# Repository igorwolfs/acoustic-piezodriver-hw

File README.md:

# Acoustic Piezodriver HW

This board generates the signal used to excite the piezo-module. Excitation frequencies are between 100 kHz and 10 MHz. All above 5 MHz will probably be hard to reach, given the component specs had to be balanced with price.

## 40V BOOST
Supplies the single-phase inverter with a 40 V voltage, given a 20 V input voltage.

## 6V SEPIC
Supplies around 6 V to the PCONN 5V connector. Meant to supply power to the acoustic-processing-hw board.

## 10 V SEPIC
Supplies the FET-drivers with a steady 10V.

## SIGCONN
Drives the PWM signals, enables the 40V BOOST and the 10V SEPIC, contains an SPI bus meant to control the on-board ADC and temperature sensors. Meant to be connected to the acoustic-processing-hw board.

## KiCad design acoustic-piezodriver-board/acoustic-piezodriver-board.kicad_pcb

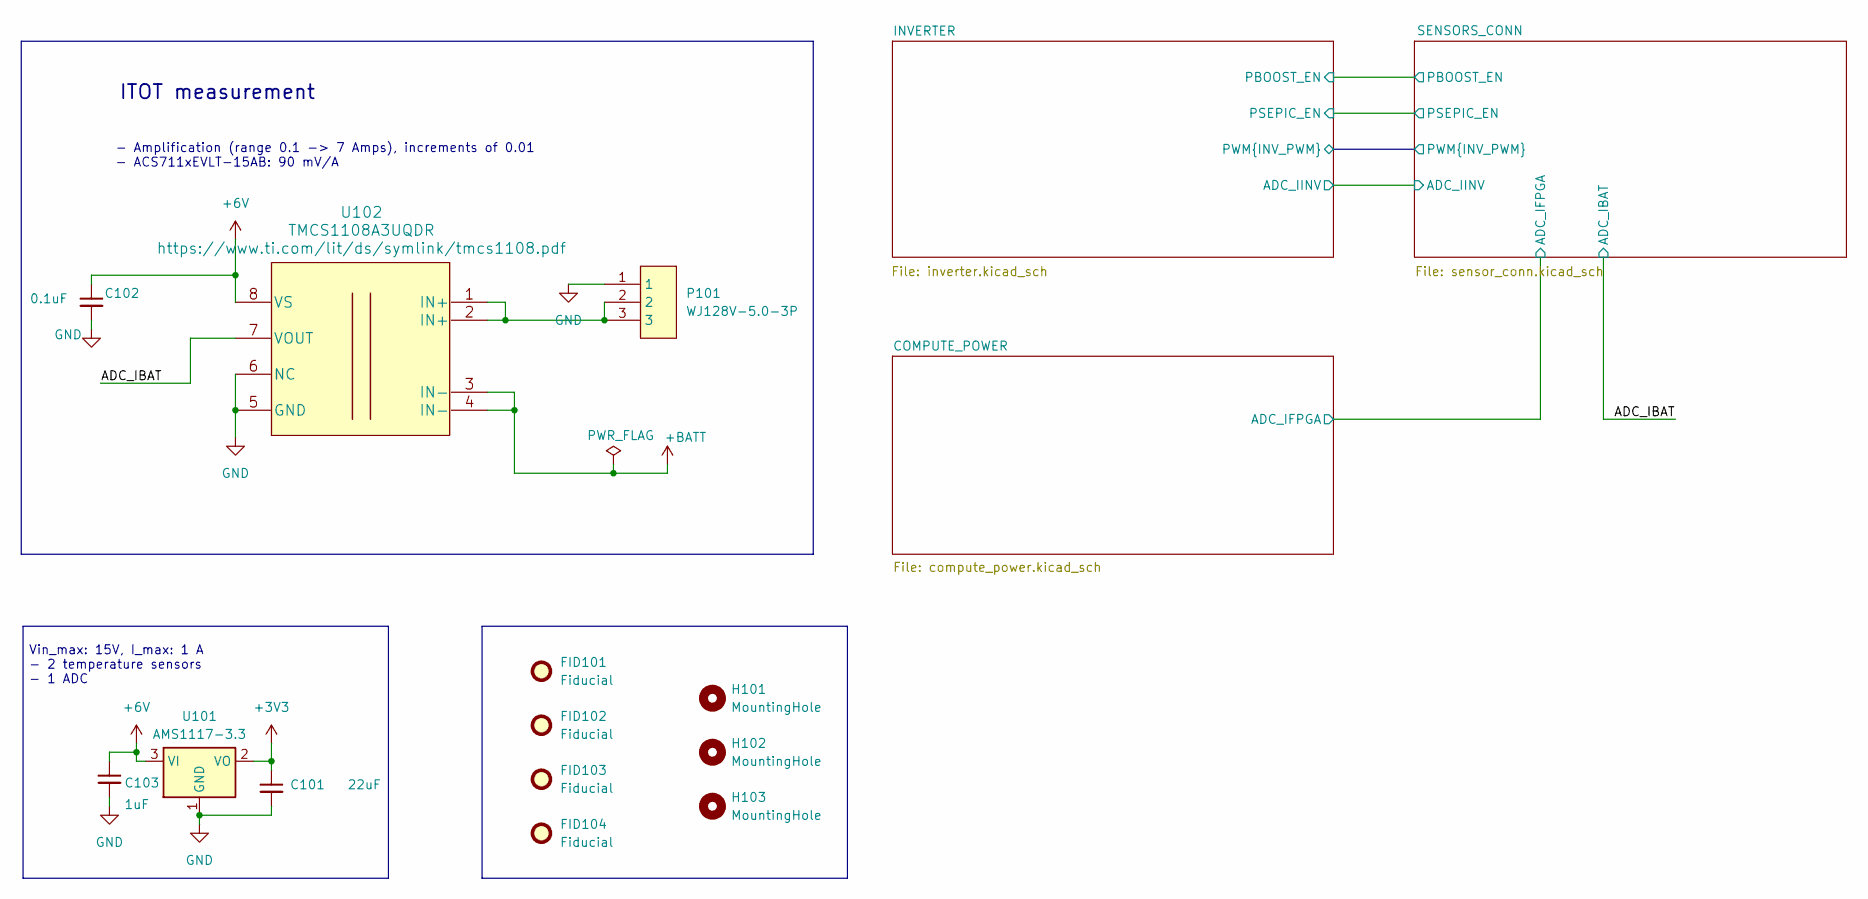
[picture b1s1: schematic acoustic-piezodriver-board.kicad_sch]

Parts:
C101: 22uF; C_0805_2012Metric; Manufacturing Part Numb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 CL21A226MAQNNNE; LCSC Part Number C45783
C102: 0.1uF; C_0402_1005Metric; Manufacturing Part Numb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 CL05B104KB54PNC; LCSC Part Number C307331
C103: 1uF; C_0805_2012Metric; Manufacturing Part Numb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 CL21B105KBFNNNE; LCSC Part Number C28323
FID101, FID102, FID103, FID104: Fiducial; Fiducial_1mm_Mask2mm
H101, H102, H103: MountingHole; ToolingHole_1.152mm
P101: WJ128V-5.0-3P; Manufacturing Part Numb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 WJ128V-5.0-3P; LCSC Part Number C8270
U101: AMS1117-3.3; SOT-223-3_TabPin2; Manufacturing Part Numb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 AMS1117-3.3; LCSC Part Number C6186
U102: TMCS1108A3UQDR; Manufacturing Part Numb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 TMCS1108A3UQDR; LCSC Part Number C3684263

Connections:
+3V3: C101.1, U101.2 (VO); also elsewhere on the board
+6V: C102.1, C103.1, U101.3 (VI), U102.8 (VS); also elsewhere on the board
+BATT: U102.3 (IN-), U102.4 (IN-); also elsewhere on the board
/ADC_IBAT: U102.7 (VOUT); also elsewhere on the board
GND: C101.2, C102.2, C103.2, P101.1, U101.1 (GND), U102.5 (GND), U102.6 (NC); also elsewhere on the board
unnamed: P101.2, P101.3, U102.1 (IN+), U102.2 (IN+)

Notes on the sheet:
ITOT measurement
- Amplification (range 0.1 -> 7 Amps), increments of 0.01 - ACS711xEVLT-15AB: 90 mV/A
Vin_max: 15V, I_max: 1 A - 2 temperature sensors - 1 ADC

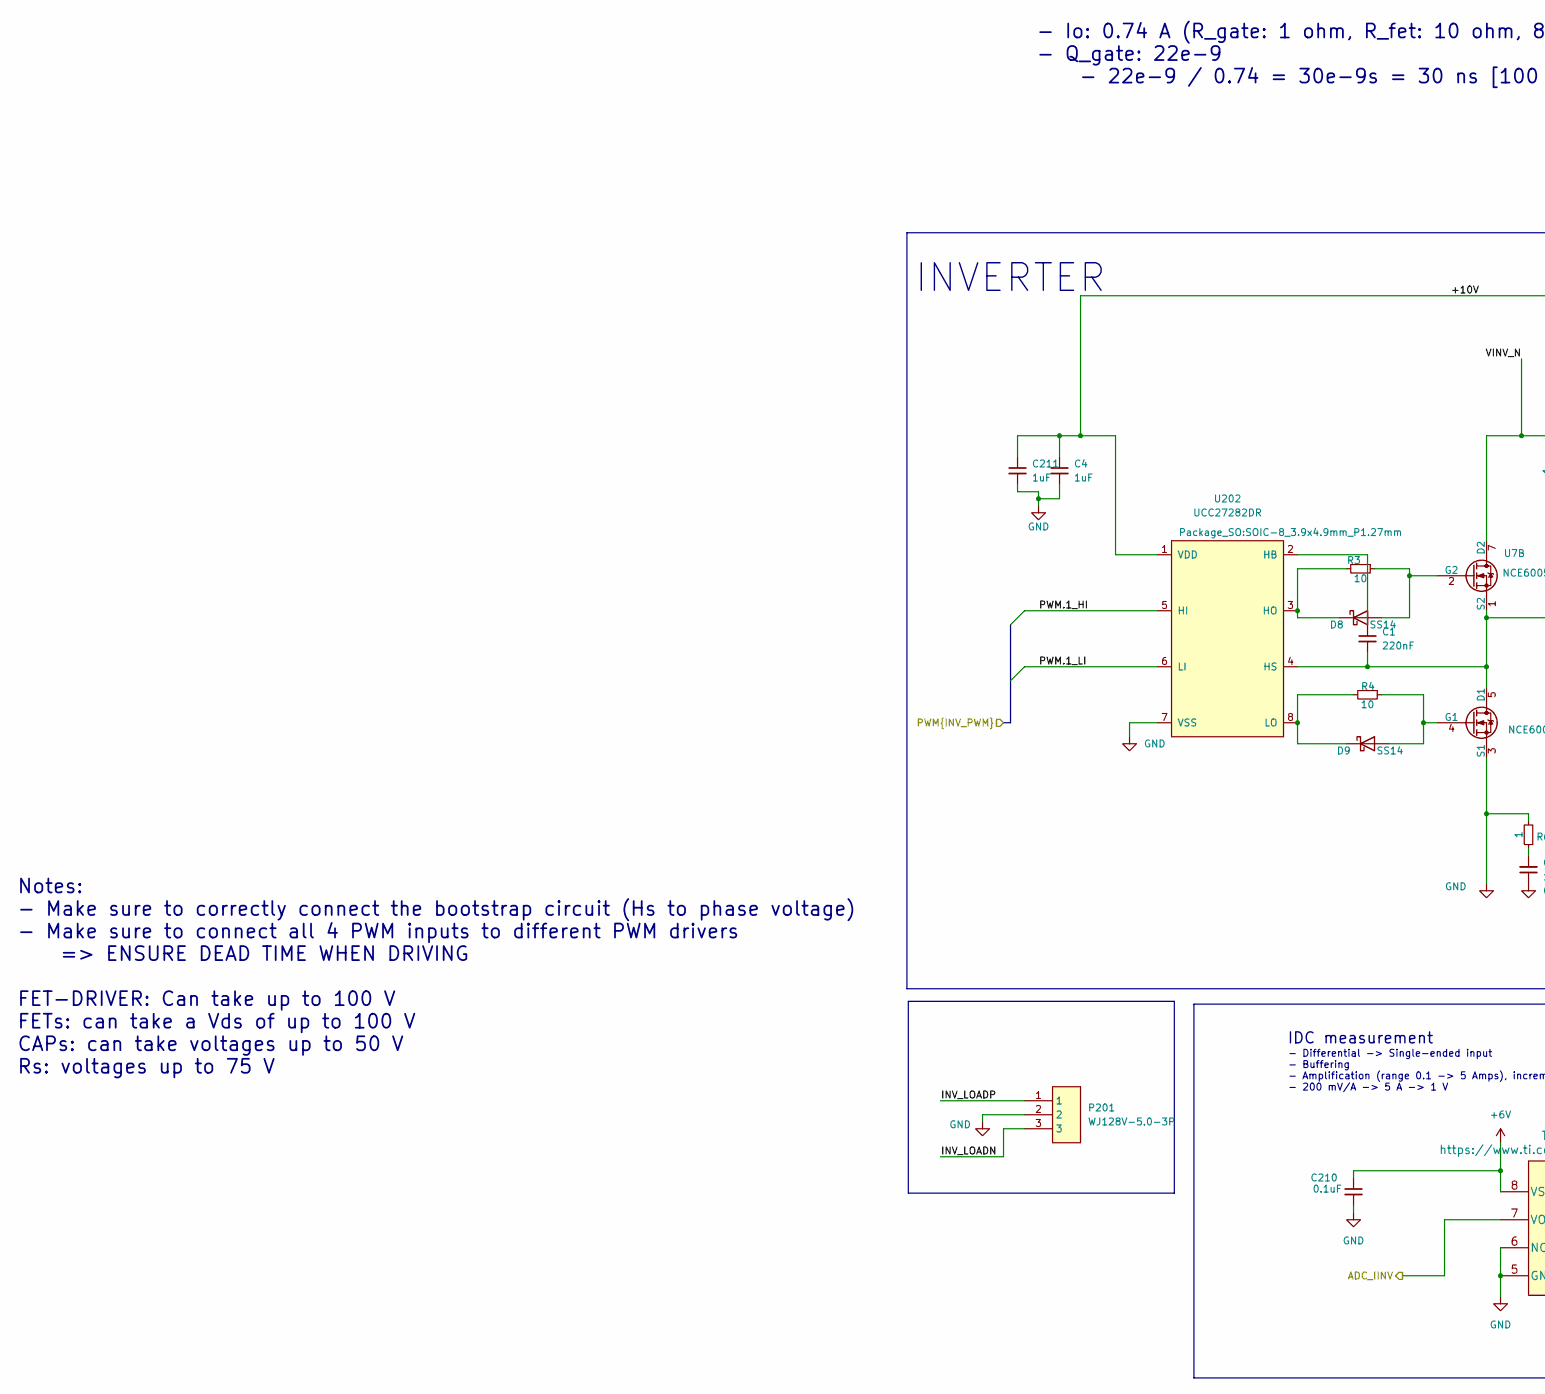
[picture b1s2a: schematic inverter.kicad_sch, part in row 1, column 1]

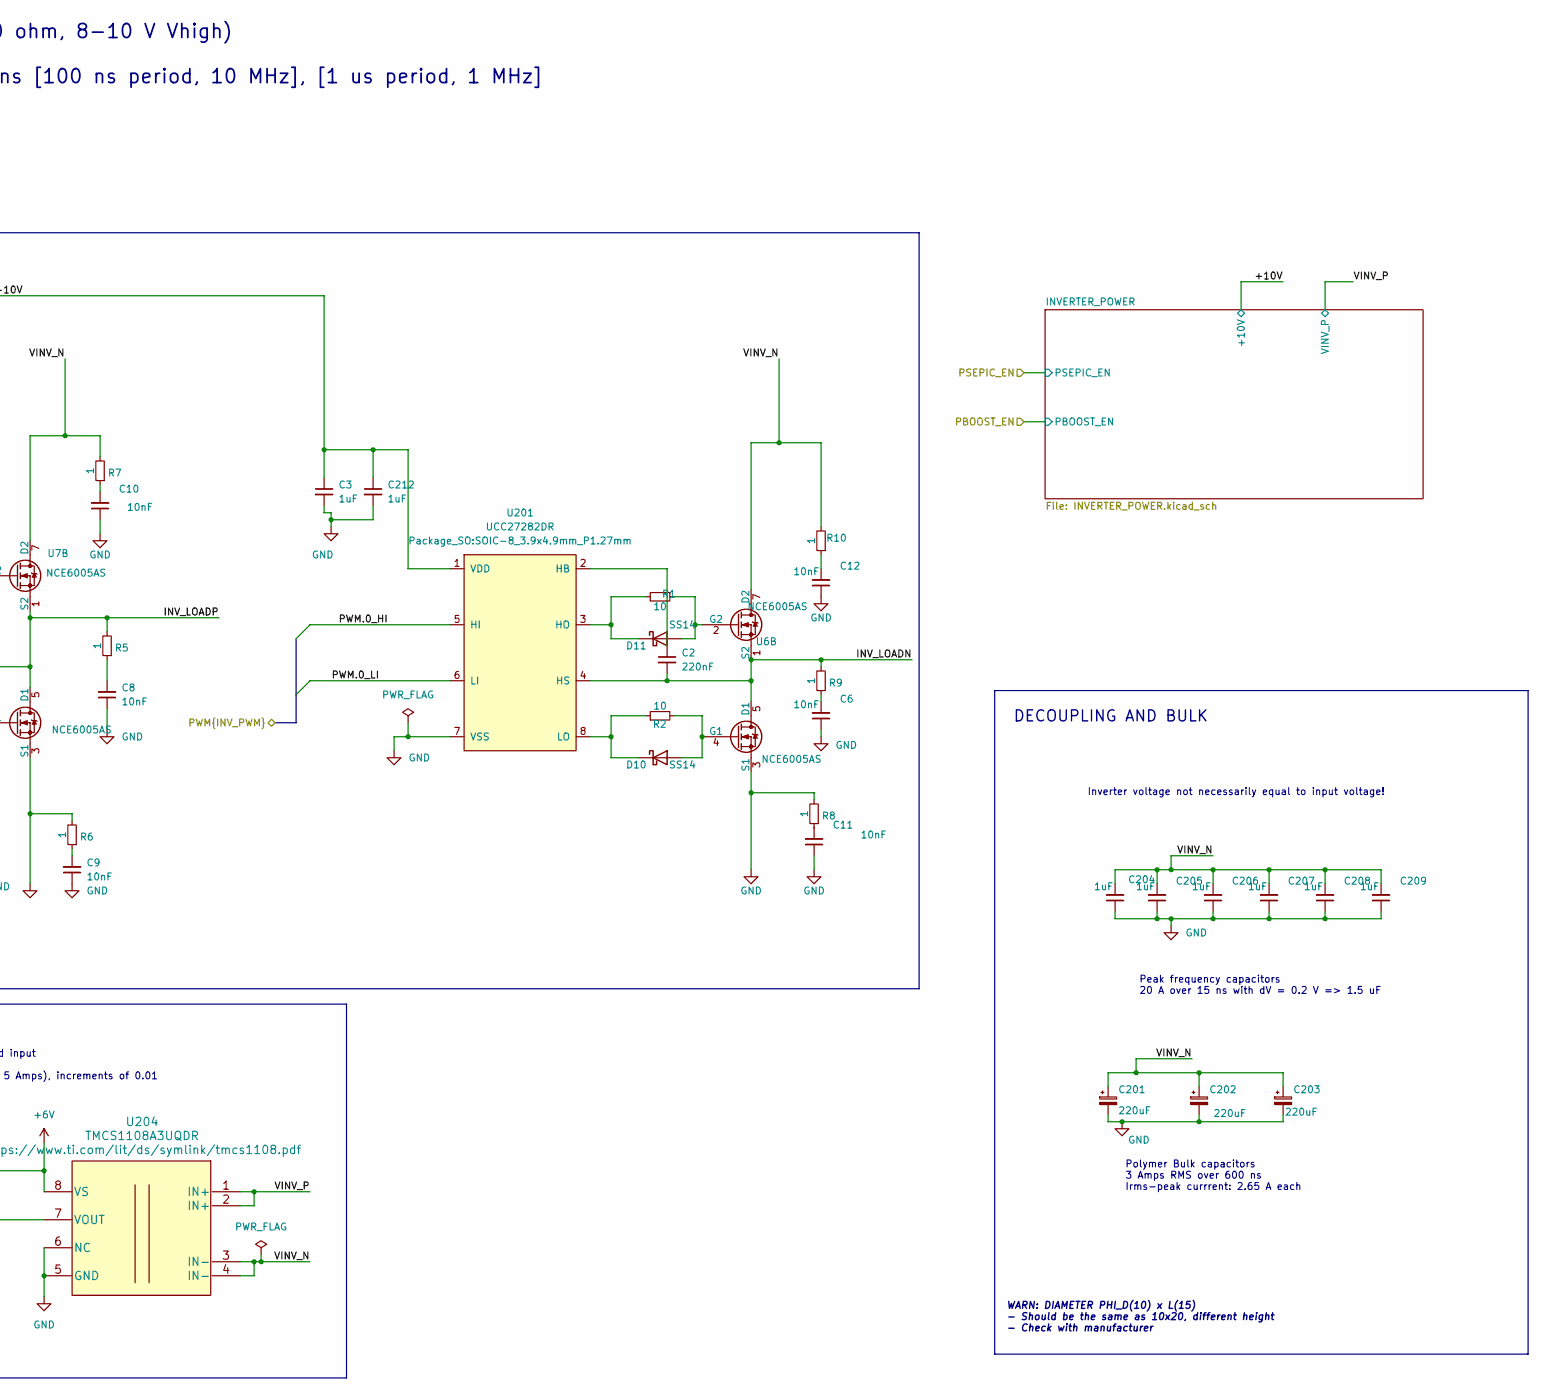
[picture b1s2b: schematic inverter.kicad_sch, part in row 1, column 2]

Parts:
C1, C2: 220nF; C_0805_2012Metric; Manufacturing Part Numb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 CL21B224KBFNNNE; LCSC Part Number C5378
C3, C4, C204, C205, C206, C207, C208, C209, C211, C212: 1uF; C_0805_2012Metric; Manufacturing Part Numb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 CL21B105KBFNNNE; LCSC Part Number C28323
C6, C8, C9, C10, C11, C12: 10nF; C_0402_1005Metric; Manufacturing Part Numb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 CL05B103KB5NNNC; LCSC Part Number C15195
C201, C202, C203: 220uF; C_Radial_D10.0mm_H16.0mm_P5.00mm; Manufacturing Part Numb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 SPZ1JM221G15O00RAXXX; LCSC Part Number C2983797
C210: 0.1uF; C_0402_1005Metric; Manufacturing Part Numb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 CL05B104KB54PNC; LCSC Part Number C307331
D8, D9, D10, D11: SS14; D_SMA; Manufacturing Part Numb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 SS14; LCSC Part Number C2480
P201: WJ128V-5.0-3P; Manufacturing Part Numb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 WJ128V-5.0-3P; LCSC Part Number C8270
R1, R2, R3, R4: 10; R_1206_3216Metric; Manufacturing Part Numb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 1206W4F100JT5E; LCSC Part Number C17903
R5, R6, R7, R8, R9, R10: 1; R_0603_1608Metric; Manufacturing Part Numb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 0603WAF100KT5E; LCSC Part Number C22936
U6, U7: NCE6005AS; SOIC-8_3.9x4.9mm_P1.27mm; Manufacturing Part Numb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 NCE6005AS; LCSC Part Number C126151
U201, U202: UCC27282DR; SOIC-8_3.9x4.9mm_P1.27mm; Manufacturing Part Numb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 UCC27282DR; LCSC Part Number C2867844
U204: TMCS1108A3UQDR; Manufacturing Part Numb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 TMCS1108A3UQDR; LCSC Part Number C3684263

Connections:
+6V: C210.1, U204.8 (VS); also elsewhere on the board
/INVERTER/+10V: C3.1, C4.1, C211.1, C212.1, U201.1 (VDD), U202.1 (VDD); also elsewhere on the board
/INVERTER/ADC_IINV: U204.7 (VOUT); also elsewhere on the board
/INVERTER/INV_LOADN: C2.2, P201.3, R9.2, U6.1 (S2), U6.5 (D1), U6.6 (D1), U201.4 (HS)
/INVERTER/INV_LOADP: C1.2, P201.1, R5.2, U7.1 (S2), U7.5 (D1), U7.6 (D1), U202.4 (HS)
/INVERTER/PWM.0_HI: U201.5 (HI); also elsewhere on the board
/INVERTER/PWM.0_LI: U201.6 (LI); also elsewhere on the board
/INVERTER/PWM.1_HI: U202.5 (HI); also elsewhere on the board
/INVERTER/PWM.1_LI: U202.6 (LI); also elsewhere on the board
/INVERTER/VINV_N: C201.1, C202.1, C203.1, C204.2, C205.2, C206.2, C207.2, C208.2, C209.2, R7.2, R10.2, U6.7 (D2), U6.8 (D2), U7.7 (D2), U7.8 (D2), U204.3 (IN-), U204.4 (IN-)
/INVERTER/VINV_P: U204.1 (IN+), U204.2 (IN+); also elsewhere on the board
GND: C3.2, C4.2, C6.1, C8.1, C9.1, C10.1, C11.1, C12.1, C201.2, C202.2, C203.2, C204.1, C205.1, C206.1, C207.1, C208.1, C209.1, C210.2, C211.2, C212.2, P201.2, R6.2, R8.2, U6.3 (S1), U7.3 (S1), U201.7 (VSS), U202.7 (VSS), U204.5 (GND), U204.6 (NC); also elsewhere on the board
unnamed: C6.2, R9.1
unnamed: C8.2, R5.1
unnamed: C9.2, R6.1
unnamed: C10.2, R7.1
unnamed: C11.2, R8.1
unnamed: C12.2, R10.1
unnamed: D8.2 (A), R3.1, U7.2 (G2)
unnamed: D8.1 (K), R3.2, U202.3 (HO)
unnamed: D9.2 (A), R4.1, U7.4 (G1)
unnamed: D9.1 (K), R4.2, U202.8 (LO)
unnamed: D10.2 (A), R2.2, U6.4 (G1)
unnamed: D10.1 (K), R2.1, U201.8 (LO)
unnamed: D11.2 (A), R1.1, U6.2 (G2)
unnamed: D11.1 (K), R1.2, U201.3 (HO)
unnamed: C2.1, U201.2 (HB)
unnamed: C1.1, U202.2 (HB)

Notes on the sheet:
- Io: 0.74 A (R_gate: 1 ohm, R_fet: 10 ohm, 8-10 V Vhigh) - Q_gate: 22e-9 - 22e-9 / 0.74 = 30e-9s = 30 ns [100 ns period, 10 MHz], [1 us period, 1 MHz]
DECOUPLING AND BULK
INVERTER
Peak frequency capacitors 20 A over 15 ns with dV = 0.2 V => 1.5 uF
- Differential -> Single-ended input - Buffering - Amplification (range 0.1 -> 5 Amps), increments of 0.01 - 200 mV/A -> 5 A -> 1 V
Notes: - Make sure to correctly connect the bootstrap circuit (Hs to phase voltage) - Make sure to connect all 4 PWM inputs to different PWM drivers => ENSURE DEAD TIME WHEN DRIVING FET-DRIVER: Can take up to 100 V FETs: can take a Vds of up to 100 V CAPs: can take voltages up to 50 V Rs: voltages 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
Polymer Bulk capacitors 3 Amps RMS over 600 ns Irms-peak currrent: 2.65 A each
Inverter voltage not necessarily equal to input voltage!
WARN: DIAMETER PHI_D(10) x L(15) - Should be the same as 10x20, different height - Check with manufacturer
IDC measurement

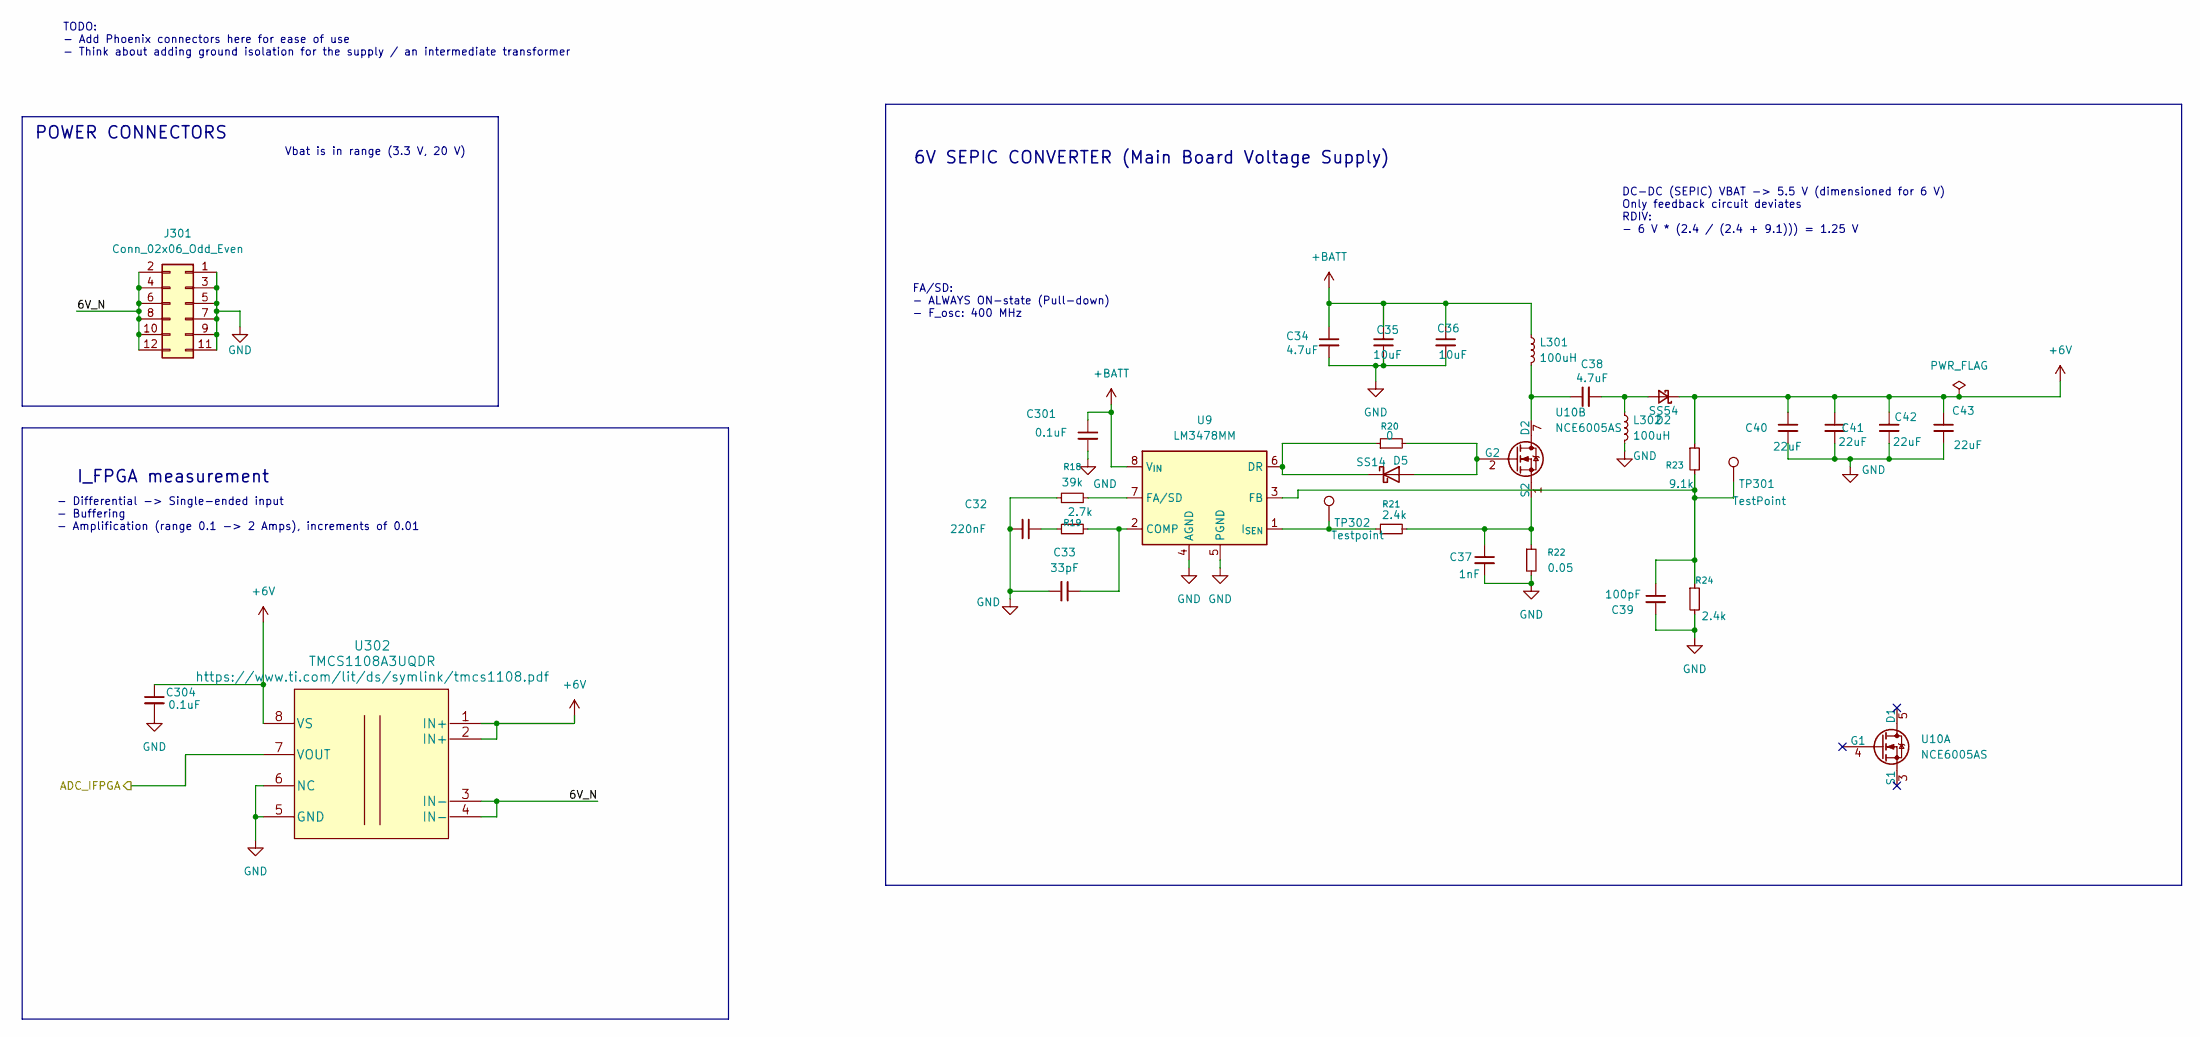
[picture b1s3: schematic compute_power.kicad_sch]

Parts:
C32: 220nF; C_0805_2012Metric; Manufacturing Part Numb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 CL21B224KBFNNNE; LCSC Part Number C5378
C33: 33pF; C_0603_1608Metric; Manufacturing Part Numb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 CL10C330JB8NNNC; LCSC Part Number C1663
C34, C38: 4.7uF; C_1206_3216Metric; Manufacturing Part Numb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 1206B475K500NT; LCSC Part Number C29823
C35, C36: 10uF; C_0805_2012Metric; Manufacturing Part Numb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 GRM21BR61H106KE43L; LCSC Part Number C440198
C37: 1nF; C_0402_1005Metric; Manufacturing Part Numb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 0402B102K500NT; LCSC Part Number C1523
C39: 100pF; C_0402_1005Metric; Manufacturing Part Numb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 0402CG101J500NT; LCSC Part Number C1546
C40, C41, C42, C43: 22uF; C_0805_2012Metric; Manufacturing Part Numb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 CL21A226MAQNNNE; LCSC Part Number C45783
C301, C304: 0.1uF; C_0402_1005Metric; Manufacturing Part Numb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 CL05B104KB54PNC; LCSC Part Number C307331
D2: SS54; D_SMA; Manufacturing Part Numb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 SS54; LCSC Part Number C22452
D5: SS14; D_SMA; Manufacturing Part Numb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 SS14; LCSC Part Number C2480
J301: Conn_02x06_Odd_Even; PinHeader_2x06_P2.54mm_Vertical; Manufacturing Part Numb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 B-2100S12P-B110; LCSC Part Number C124388
L301, L302: 100uH; PSPMAA1050H-101M-ANP; Manufacturing Part Numb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 PSPMAA1050H-101M-ANP; LCSC Part Number C5273830
R18: 39k; R_0603_1608Metric; Manufacturing Part Numb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 0603WAF3902T5E; LCSC Part Number C23153
R19: 2.7k; R_0603_1608Metric; Manufacturing Part Numb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 0603WAF2701T5E; LCSC Part Number C13167
R20: 0; R_0603_1608Metric_Pad0.98x0.95mm_HandSolder; Manufacturing Part Numb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 0603WAJ0000T5E; LCSC Part Number C15402
R21: 2.4k; R_0805_2012Metric_Pad1.20x1.40mm_HandSolder; Manufacturing Part Numb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 0805W8F2401T5E; LCSC Part Number C17526
R22: 0.05; R_1206_3216Metric_Pad1.30x1.75mm_HandSolder; Manufacturing Part Numb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 1206W3F500MT5E; LCSC Part Number C127691
R23: 9.1k; R_0603_1608Metric; Manufacturing Part Numb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 0603WAF9101T5E; LCSC Part Number C23260
R24: 2.4k; R_0603_1608Metric; Manufacturing Part Numb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 0603WAF2401T5E; LCSC Part Number C22940
TP301: TestPoint; TestPoint_Pad_D1.0mm
TP302: Testpoint; TestPoint_Pad_D1.0mm
U9: LM3478MM; VSSOP-8_3x3mm_P0.65mm; Manufacturing Part Numb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 LM3478MMX/NOPB; LCSC Part Number C404045
U10: NCE6005AS; SOIC-8_3.9x4.9mm_P1.27mm; Manufacturing Part Numb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 NCE6005AS; LCSC Part Number C126151
U302: TMCS1108A3UQDR; Manufacturing Part Numb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 TMCS1108A3UQDR; LCSC Part Number C3684263

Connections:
+6V: C40.1, C41.1, C42.1, C43.1, C304.1, D2.1 (K), R23.1, U302.1 (IN+), U302.2 (IN+), U302.8 (VS); also elsewhere on the board
+BATT: C34.1, C35.1, C36.1, C301.1, L301.1, U9.8 (V_{IN}); also elsewhere on the board
/COMPUTE_POWER/6V_N: J301.2, J301.4, J301.6, J301.8, J301.10, J301.12, U302.3 (IN-), U302.4 (IN-)
/COMPUTE_POWER/ADC_IFPGA: U302.7 (VOUT); also elsewhere on the board
GND: C32.2, C33.2, C34.2, C35.2, C36.2, C37.2, C39.2, C40.2, C41.2, C42.2, C43.2, C301.2, C304.2, J301.1, J301.3, J301.5, J301.7, J301.9, J301.11, L302.2, R18.1, R22.2, R24.2, U9.4 (AGND), U9.5 (PGND), U302.5 (GND), U302.6 (NC); also elsewhere on the board
unnamed: C32.1, R19.1
unnamed: C38.1, L301.2, U10.7 (D2), U10.8 (D2)
unnamed: C38.2, D2.2 (A), L302.1
unnamed: D5.2 (A), R20.2, U10.2 (G2)
unnamed: D5.1 (K), R20.1, U9.6 (DR)
unnamed: C33.1, R19.2, U9.2 (COMP)
unnamed: R18.2, U9.7 (FA/SD)
unnamed: C39.1, R23.2, R24.1, TP301.1, U9.3 (FB)
unnamed: R21.1, TP302.1, U9.1 (I_{SEN})
unnamed: C37.1, R21.2, R22.1, U10.1 (S2)

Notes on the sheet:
POWER CONNECTORS
I_FPGA measurement
DC-DC (SEPIC) VBAT -> 5.5 V (dimensioned for 6 V) Only feedback circuit deviates RDIV: - 6 V * (2.4 / (2.4 + 9.1))) = 1.25 V
Vbat is in range (3.3 V, 20 V)
- Differential -> Single-ended input - Buffering - Amplification (range 0.1 -> 2 Amps), increments of 0.01
6V SEPIC CONVERTER (Main Board Voltage Supply)
TODO: - Add Phoenix connectors here for ease of use - Think about adding ground isolation for the supply / an intermediate transformer
FA/SD: - ALWAYS ON-state (Pull-down) - F_osc: 400 MHz

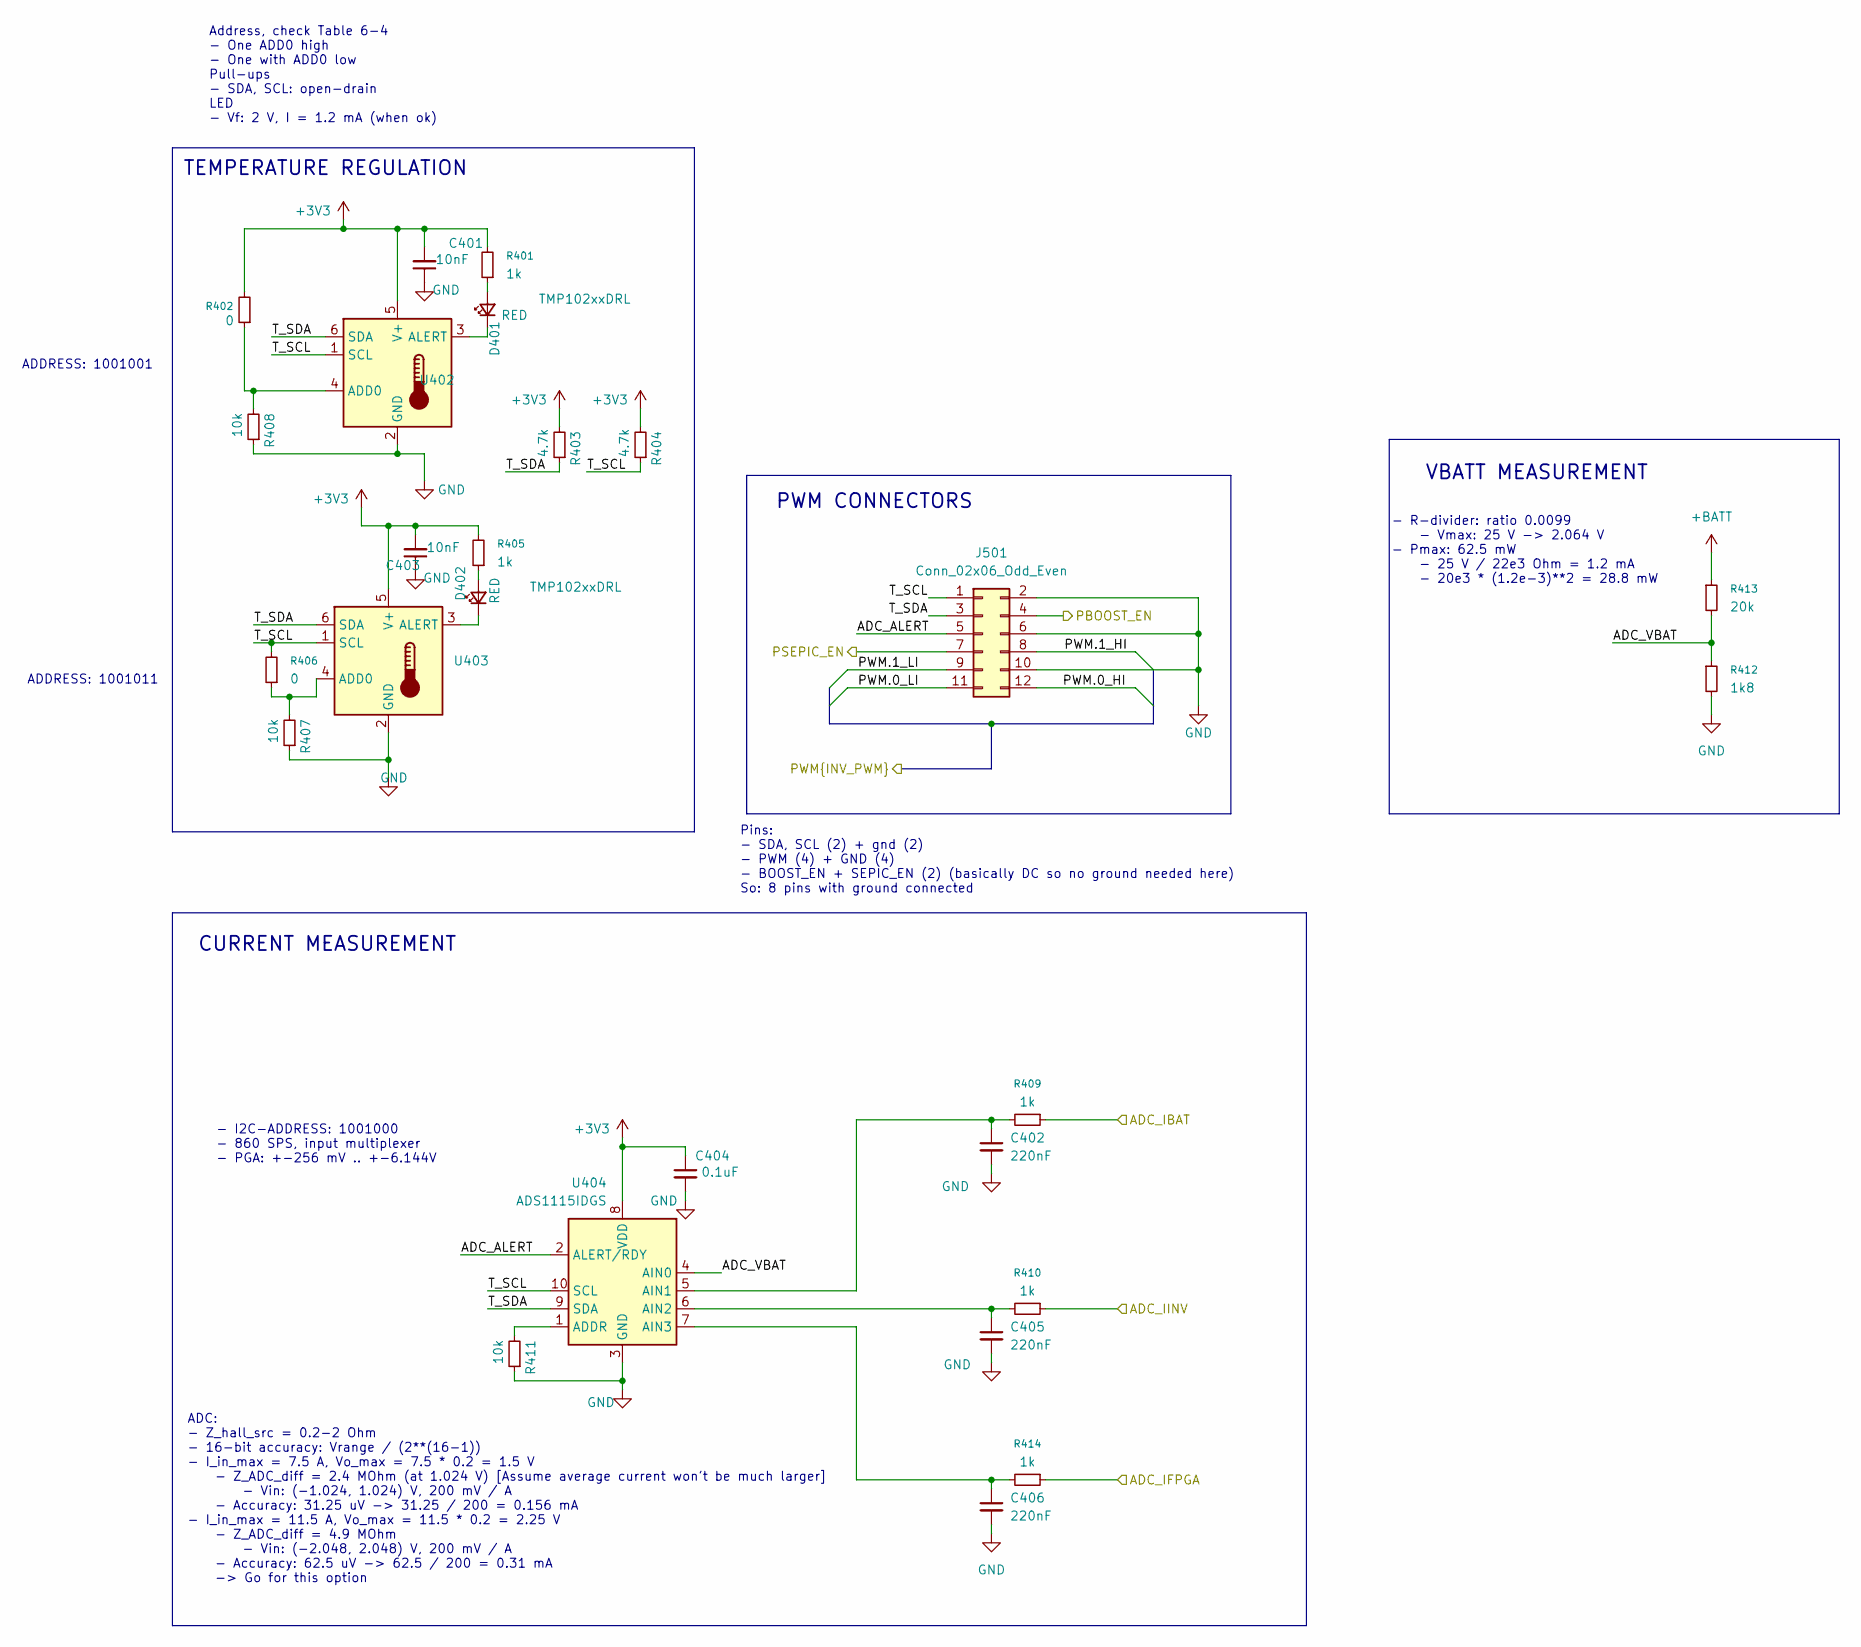
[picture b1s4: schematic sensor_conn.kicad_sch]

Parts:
C401, C403: 10nF; C_0402_1005Metric; Manufacturing Part Numb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 CL05B103KB5NNNC; LCSC Part Number C15195
C402, C405, C406: 220nF; C_0402_1005Metric; Manufacturing Part Numb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 CL05B224KO5NNNC; LCSC Part Number C16772
C404: 0.1uF; C_0402_1005Metric; Manufacturing Part Numb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 CL05B104KB54PNC; LCSC Part Number C307331
D401, D402: RED; LED_0603_1608Metric; Manufacturing Part Numb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 KT-0603R; LCSC Part Number C2286
J501: Conn_02x06_Odd_Even; PinHeader_2x06_P2.54mm_Vertical; Manufacturing Part Numb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 B-2100S12P-B110; LCSC Part Number C124388
R401, R405, R409, R410, R414: 1k; R_0402_1005Metric; Manufacturing Part Numb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 0402WGF1001TCE; LCSC Part Number C11702
R402, R406: 0; R_0603_1608Metric_Pad0.98x0.95mm_HandSolder; Manufacturing Part Numb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 0603WAJ0000T5E; LCSC Part Number C15402
R403, R404: 4.7k; R_0402_1005Metric; Manufacturing Part Numb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 0402WGF4701TCE; LCSC Part Number C25900
R407, R408, R411: 10k; R_0603_1608Metric; Manufacturing Part Numb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 0603WAJ0103T5E; LCSC Part Number C15401
R412: 1k8; R_0603_1608Metric; Manufacturing Part Numb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 0603WAF1801T5E; LCSC Part Number C4177
R413: 20k; R_0402_1005Metric; Manufacturing Part Numb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 0402WGF2002TCE; LCSC Part Number C25765
U402, U403: TMP102xxDRL; SOT-563; Manufacturing Part Numb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 TMP102AIDRLR; LCSC Part Number C99269
U404: ADS1115IDGS; TSSOP-10_3x3mm_P0.5mm; Manufacturing Part Numb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 ADS1115IDGSR; LCSC Part Number C37593

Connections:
+3V3: C401.2, C403.2, C404.1, R401.2, R402.2, R403.2, R404.2, R405.2, U402.5 (V+), U403.5 (V+), U404.8 (VDD); also elsewhere on the board
+BATT: R413.1; also elsewhere on the board
/ADC_IBAT: R409.1; also elsewhere on the board
/COMPUTE_POWER/ADC_IFPGA: R414.1; also elsewhere on the board
/INVERTER/ADC_IINV: R410.1; also elsewhere on the board
/INVERTER/PBOOST_EN: J501.4; also elsewhere on the board
/INVERTER/PSEPIC_EN: J501.7; also elsewhere on the board
/INVERTER/PWM.0_HI: J501.12; also elsewhere on the board
/INVERTER/PWM.0_LI: J501.11; also elsewhere on the board
/INVERTER/PWM.1_HI: J501.8; also elsewhere on the board
/INVERTER/PWM.1_LI: J501.9; also elsewhere on the board
/SENSORS_CONN/ADC_ALERT: J501.5, U404.2 (ALERT/RDY)
/SENSORS_CONN/ADC_VBAT: R412.1, R413.2, U404.4 (AIN0)
/SENSORS_CONN/T_SCL: J501.1, R404.1, R406.2, U402.1 (SCL), U403.1 (SCL), U404.10 (SCL)
/SENSORS_CONN/T_SDA: J501.3, R403.1, U402.6 (SDA), U403.6 (SDA), U404.9 (SDA)
GND: C401.1, C402.2, C403.1, C404.2, C405.2, C406.2, J501.2, J501.6, J501.10, R407.1, R408.1, R411.1, R412.2, U402.2 (GND), U403.2 (GND), U404.3 (GND); also elsewhere on the board
unnamed: D401.2 (A), R401.1
unnamed: D401.1 (K), U402.3 (ALERT)
unnamed: D402.2 (A), R405.1
unnamed: D402.1 (K), U403.3 (ALERT)
unnamed: R402.1, R408.2, U402.4 (ADD0)
unnamed: R406.1, R407.2, U403.4 (ADD0)
unnamed: R411.2, U404.1 (ADDR)
unnamed: C402.1, R409.2, U404.5 (AIN1)
unnamed: C405.1, R410.2, U404.6 (AIN2)
unnamed: C406.1, R414.2, U404.7 (AIN3)

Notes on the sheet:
- I2C-ADDRESS: 1001000 - 860 SPS, input multiplexer - PGA: +-256 mV .. +-6.144V
Address, check Table 6-4 - One ADD0 high - One with ADD0 low Pull-ups - SDA, SCL: open-drain LED - Vf: 2 V, I = 1.2 mA (when ok)
PWM CONNECTORS
CURRENT MEASUREMENT
ADC: - Z_hall_src = 0.2-2 Ohm - 16-bit accuracy: Vrange / (2**(16-1)) - I_in_max = 7.5 A, Vo_max = 7.5 * 0.2 = 1.5 V - Z_ADC_diff = 2.4 MOhm (at 1.024 V) [Assume average current won't be much larger] - Vin: (-1.024, 1.024) V, 200 mV / A - Accuracy: 31.25 uV -> 31.25 / 200 = 0.156 mA - I_in_max = 11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
TEMPERATURE REGULATION
- R-divider: ratio 0.0099 - Vmax: 25 V -> 2.064 V - Pmax: 62.5 mW - 25 V / 22e3 Ohm = 1.2 mA - 20e3 * (1.2e-3)**2 = 28.8 mW
Pins: - SDA, SCL (2) + gnd (2) - PWM (4) + GND (4) - BOOST_EN + SEPIC_EN (2) (basically DC so no ground needed here) So: 8 pins with ground connected
VBATT MEASUREMENT
ADDRESS: 1001001
ADDRESS: 1001011
